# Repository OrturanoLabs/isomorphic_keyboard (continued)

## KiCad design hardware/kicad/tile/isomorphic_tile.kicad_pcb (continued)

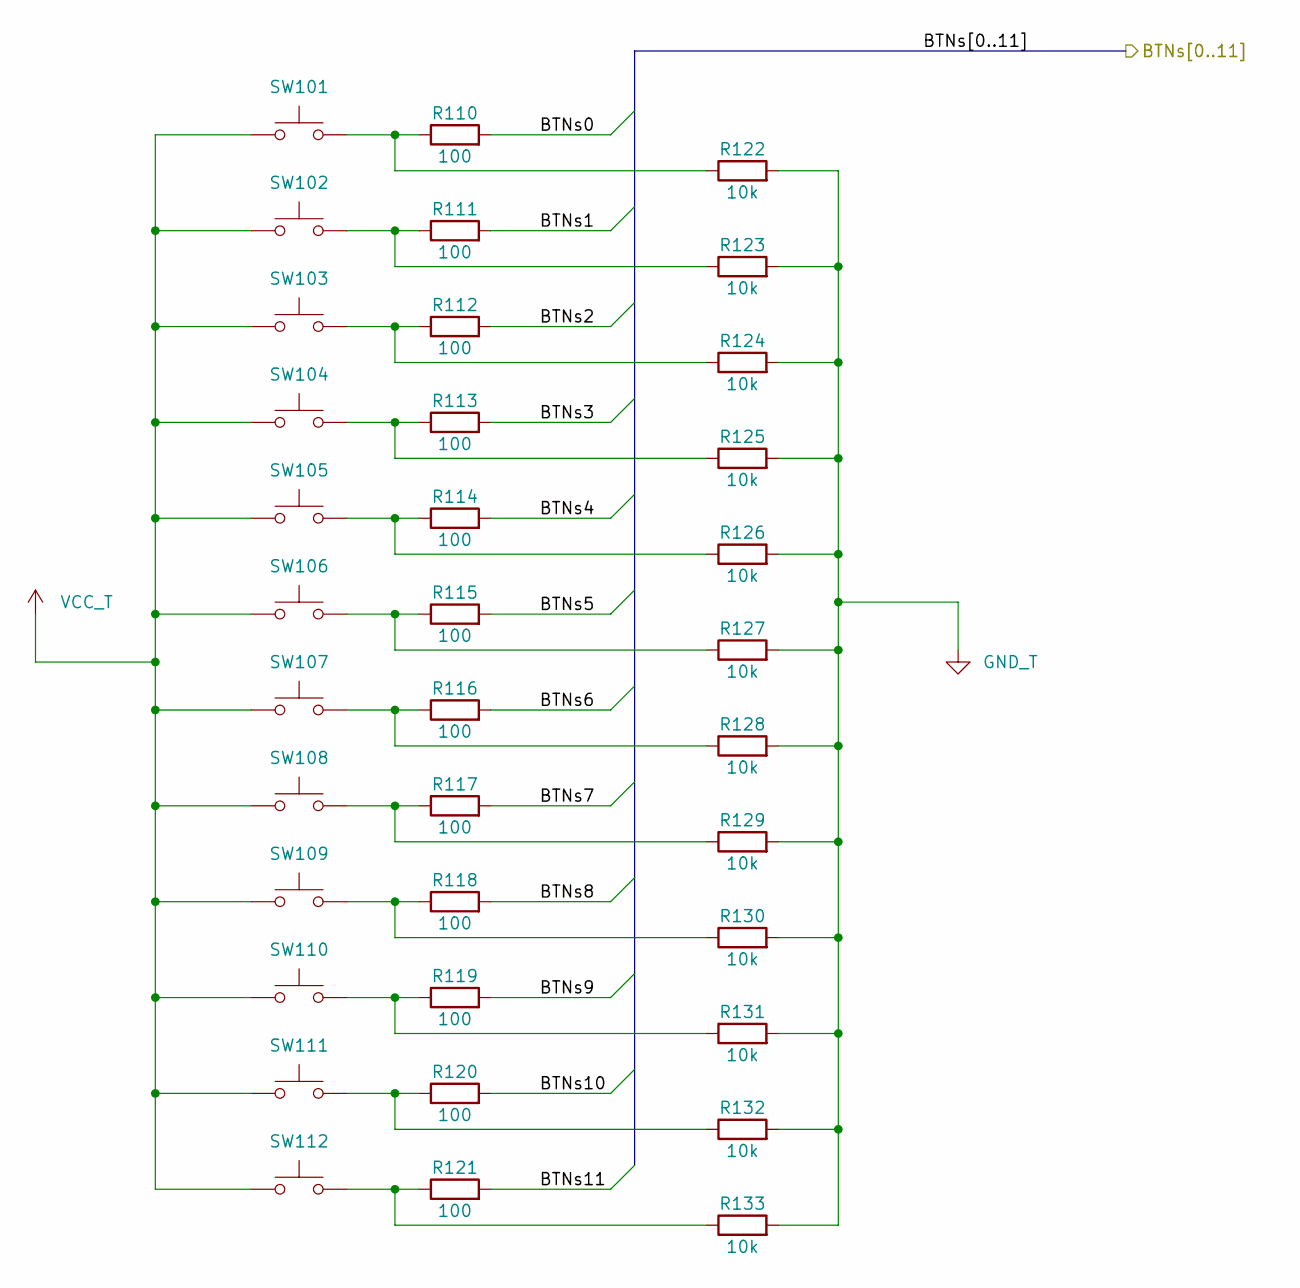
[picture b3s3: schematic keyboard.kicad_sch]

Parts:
R110, R111, R112, R113, R114, R115, R116, R117, R118, R119, R120, R121: 100; R_0603_1608Metric; MPN RC0603FR-07100RL
R122, R123, R124, R125, R126, R127, R128, R129, R130, R131, R132, R133: 10k; R_0603_1608Metric; MPN RC0603FR-0710KL
SW101, SW102, SW103, SW104, SW105, SW106, SW107, SW108, SW109, SW110, SW111, SW112: SW_Push; SW_Hotswap_Kailh_MX_1.00u_EdgeTrim; MPN CPG151101S11

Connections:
/keyboard/BTNs0: R110.2; also elsewhere on the board
/keyboard/BTNs1: R111.2; also elsewhere on the board
/keyboard/BTNs2: R112.2; also elsewhere on the board
/keyboard/BTNs3: R113.2; also elsewhere on the board
/keyboard/BTNs4: R114.2; also elsewhere on the board
/keyboard/BTNs5: R115.2; also elsewhere on the board
/keyboard/BTNs6: R116.2; also elsewhere on the board
/keyboard/BTNs7: R117.2; also elsewhere on the board
/keyboard/BTNs8: R118.2; also elsewhere on the board
/keyboard/BTNs9: R119.2; also elsewhere on the board
/keyboard/BTNs10: R120.2; also elsewhere on the board
/keyboard/BTNs11: R121.2; also elsewhere on the board
GND_T: R122.2, R123.2, R124.2, R125.2, R126.2, R127.2, R128.2, R129.2, R130.2, R131.2, R132.2, R133.2; also elsewhere on the board
unnamed: R110.1, R122.1, SW101.2
unnamed: R111.1, R123.1, SW102.2
unnamed: R112.1, R124.1, SW103.2
unnamed: R113.1, R125.1, SW104.2
unnamed: R114.1, R126.1, SW105.2
unnamed: R115.1, R127.1, SW106.2
unnamed: R116.1, R128.1, SW107.2
unnamed: R117.1, R129.1, SW108.2
unnamed: R118.1, R130.1, SW109.2
unnamed: R119.1, R131.1, SW110.2
unnamed: R120.1, R132.1, SW111.2
unnamed: R121.1, R133.1, SW112.2
VCC_T: SW101.1, SW102.1, SW103.1, SW104.1, SW105.1, SW106.1, SW107.1, SW108.1, SW109.1, SW110.1, SW111.1, SW112.1; also elsewhere on the board

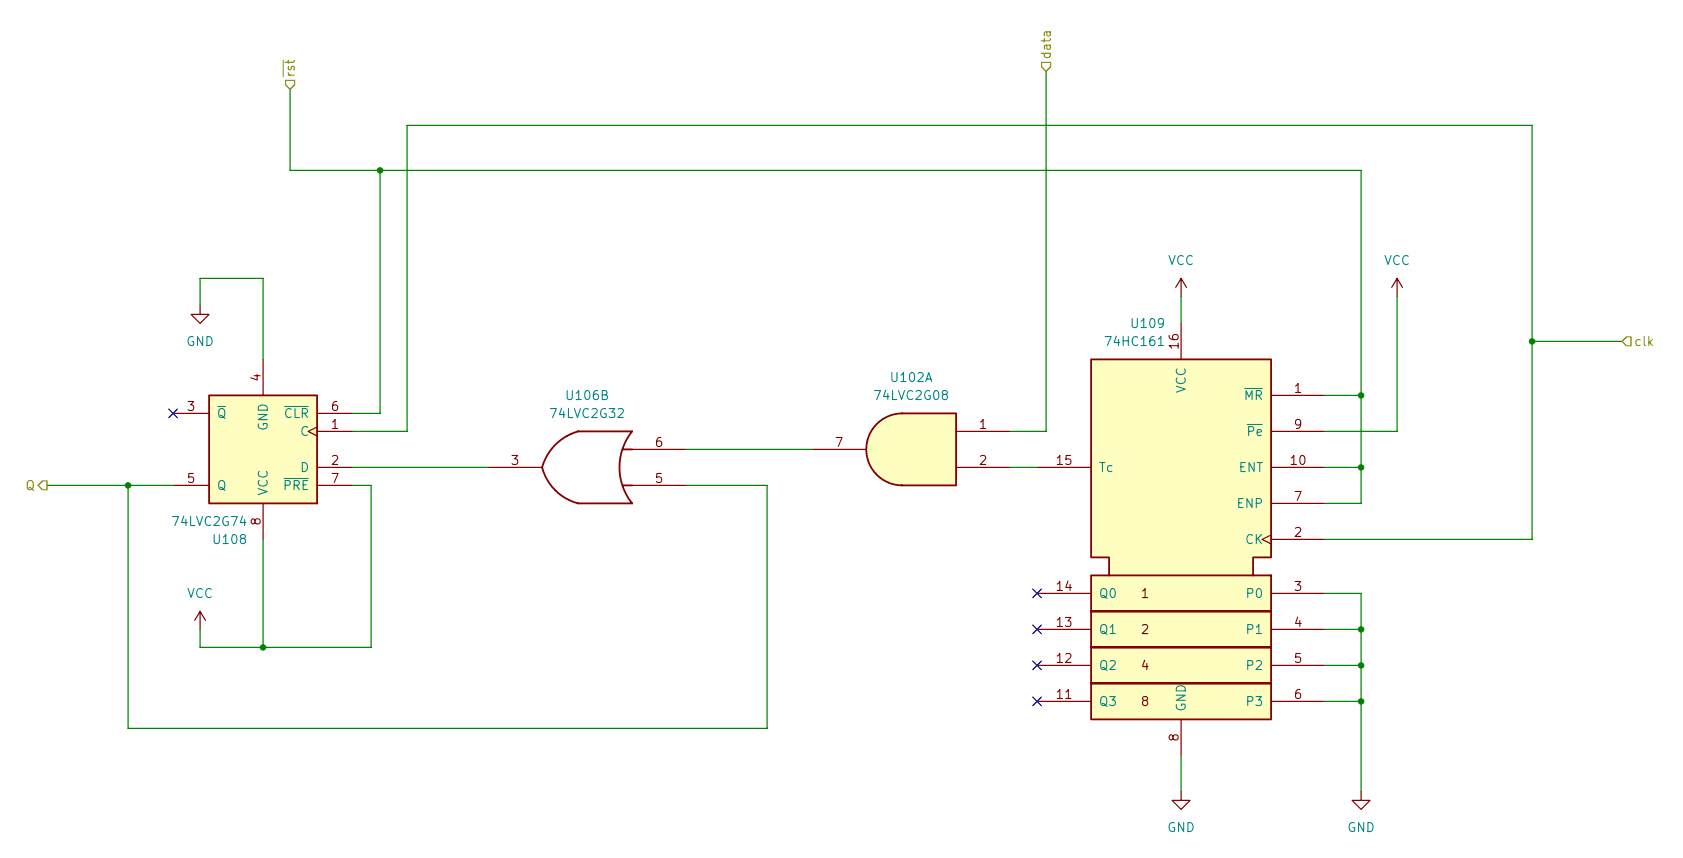
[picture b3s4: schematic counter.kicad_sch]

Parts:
U102: 74LVC2G08; SSOP-8_2.95x2.8mm_P0.65mm; MPN SN74LVC2G08DCTR
U106: 74LVC2G32; SSOP-8_2.95x2.8mm_P0.65mm; MPN SN74LVC2G32DCTR
U108: 74LVC2G74; SSOP-8_2.95x2.8mm_P0.65mm; MPN SN74LVC2G74DCTR
U109: 74HC161; SOIC-16_3.9x9.9mm_P1.27mm; MPN SN74HC161DR

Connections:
/tile/B_W_drv: U106.5, U108.5 (Q); also elsewhere on the board
/tile/B_clk: U108.1 (C), U109.2 (CK); also elsewhere on the board
/tile/counter/~rst: U108.6 (~CLR), U109.1 (~MR), U109.7 (ENP), U109.10 (ENT); also elsewhere on the board
/tile/data_drv: U102.1; also elsewhere on the board
GND: U108.4 (GND), U109.3 (P0), U109.4 (P1), U109.5 (P2), U109.6 (P3), U109.8 (GND); also elsewhere on the board
unnamed: U102.7, U106.6
unnamed: U106.3, U108.2 (D)
unnamed: U102.2, U109.15 (Tc)
VCC: U108.7 (~PRE), U108.8 (VCC), U109.9 (~Pe), U109.16 (VCC); also elsewhere on the board

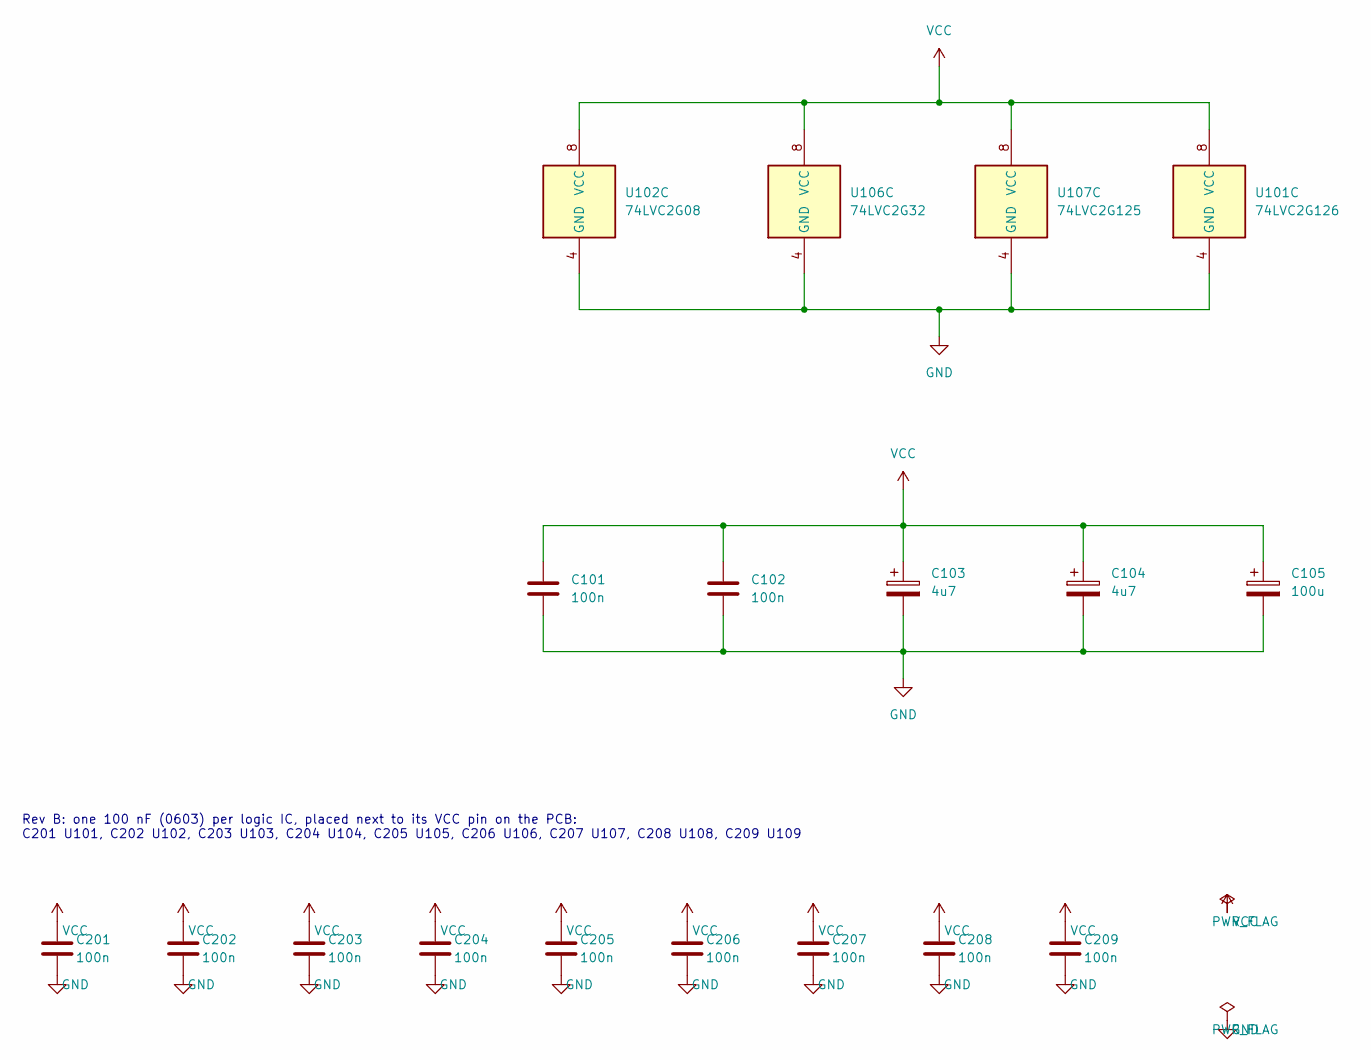
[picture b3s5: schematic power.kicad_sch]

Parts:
C101, C102, C201, C202, C203, C204, C205, C206, C207, C208, C209: 100n; C_0603_1608Metric; MPN CL10B104KB8NNNC
C103, C104: 4u7; C_1206_3216Metric; MPN CL31B475KAHNNNE
C105: 100u; CP_Elec_6.3x7.7
U101: 74LVC2G126; SSOP-8_2.95x2.8mm_P0.65mm; MPN SN74LVC2G126DCTR
U102: 74LVC2G08; SSOP-8_2.95x2.8mm_P0.65mm; MPN SN74LVC2G08DCTR
U106: 74LVC2G32; SSOP-8_2.95x2.8mm_P0.65mm; MPN SN74LVC2G32DCTR
U107: 74LVC2G125; SSOP-8_2.95x2.8mm_P0.65mm; MPN SN74LVC2G125DCTR

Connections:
GND: C101.2, C102.2, C103.2, C104.2, C105.2, C201.2, C202.2, C203.2, C204.2, C205.2, C206.2, C207.2, C208.2, C209.2, U101.4 (GND), U102.4 (GND), U106.4 (GND), U107.4 (GND); also elsewhere on the board
VCC: C101.1, C102.1, C103.1, C104.1, C105.1, C201.1, C202.1, C203.1, C204.1, C205.1, C206.1, C207.1, C208.1, C209.1, U101.8 (VCC), U102.8 (VCC), U106.8 (VCC), U107.8 (VCC); also elsewhere on the board

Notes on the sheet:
Rev B: one 100 nF (0603) per logic IC, placed next to its VCC pin on the PCB: C201 U101, C202 U102, C203 U103, C204 U104, C205 U105, C206 U106, C207 U107, C208 U108, C209 U109

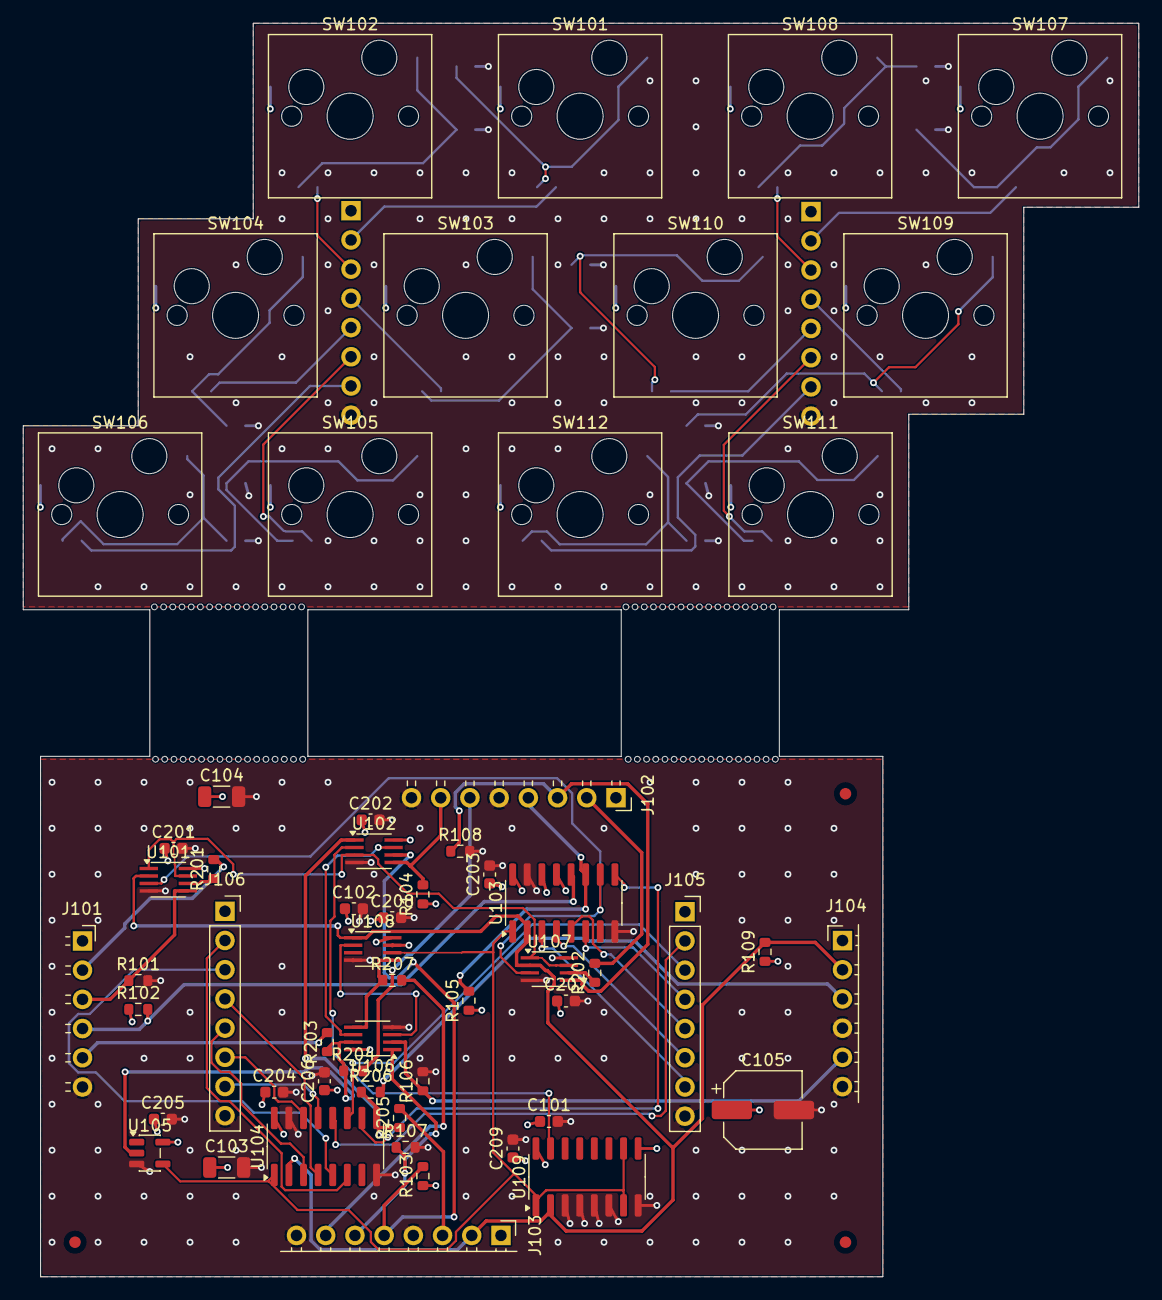
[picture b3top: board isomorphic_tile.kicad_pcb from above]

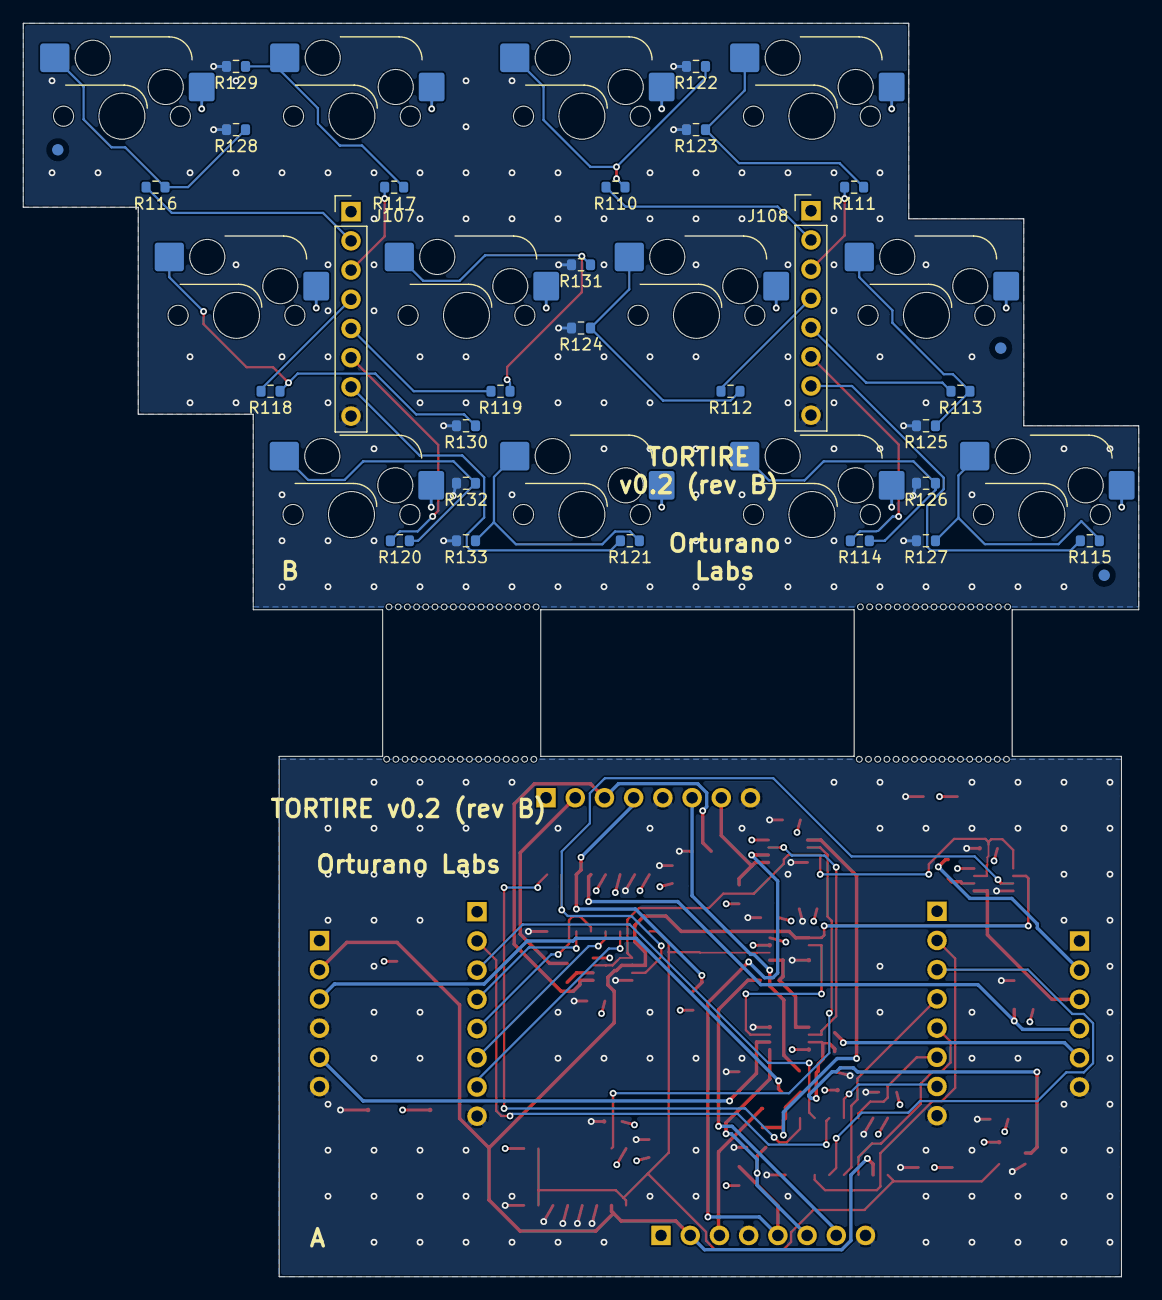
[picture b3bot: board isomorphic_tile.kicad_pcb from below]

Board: 4 copper layers, 97.0 x 109.0 mm, 157 parts (29 on the bottom side), 68 nets.

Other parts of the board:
FID1, FID2, FID3, FID4, FID5, FID6: Fiducial; Fiducial_1mm_Mask2mm
MB1, MB2, MB3, MB4, MB5, MB6, MB7, MB8, MB9, MB10, MB11, MB12, MB13, MB14, MB15, MB16, MB17, MB18, MB19, MB20, MB21, MB22, MB23, MB24, MB25, MB26, MB27, MB28, MB29, MB30, MB31, MB32, MB33, MB34, MB35, MB36, MB37, MB38, MB39, MB40, MB41, MB42, MB43, MB44, MB45, MB46, MB47, MB48, MB49, MB50, MB51, MB52, MB53, MB54, MB55, MB56, MB57, MB58, MB59, MB60, MB61, MB62, MB63, MB64, MB65, MB66, MB67, MB68: Senza-titolo; MouseBite_NPTH_0.5mm

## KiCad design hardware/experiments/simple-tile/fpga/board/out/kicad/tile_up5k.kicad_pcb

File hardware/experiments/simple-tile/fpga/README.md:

# Single-board tile: FPGA candidate experiment

One-chip-FPGA tile carrying the rev-A scan logic, replacing the 7-chip glue
+ 2x'165 + counter glue (and the 4-chip SPLD experiment) with a single FPGA.

This is an experiment, not a manufacturing-ready design. Start with
[RESULTS.md](RESULTS.md).

## Layout

- `rtl/tile_fpga.vhdl` — device-independent tile core (DUT). Selectable
  `SNAP_MODE`: "fall" (default; negedge-latch snapshot = rev-A capture
  instant, no oscillator needed) or "track" (sysclk sampling while the latch
  is high; documented approximation with a characterised dead zone).
  First-bit-before-first-clock preserved combinationally; true tri-state
  clock outputs; see docs/clock_domains.md.
- `rtl/top_{gw1nz,ice40up,ice40lp}.vhdl` + `top_*_track.vhdl` — board-level
  tops per device per mode (oscillator instantiated only for "track";
  ghdl-plugin takes no `-g`, hence the mode variants).
- `sim/` — self-checking benches + runner (`run_sims.sh`): unit scenarios
  (incl. S8 phase-sweep CHARACTERISATION), paired REF-vs-DUT grids in both
  modes, mutations.
- `rtl/top_{gw1nz,ice40up,ice40lp}.vhdl` — board-level tops: on-chip osc
  (OSCZ / SB_HFOSC) or module osc, merged connector nets, pruned straps.
- `sim/` — self-checking benches + runner (`run_sims.sh`): unit scenarios
  and paired REF(rev-A model)-vs-DUT grids with mutations.
- `synth/` — pin maps + `run_synth.sh` full flows to bitstreams.
- `docs/` — [pin budget](docs/pin_budget.md),
  [alternatives incl. TinyFPGA](docs/alternatives.md),
  [power/BOM](docs/power_bom.md), [clock domains](docs/clock_domains.md).
- `results/logs/` — pinned environment + real run logs; `results/build/`
  holds netlists/.fs/.bin (git-ignored).

## Reproduce (from the repository root)

```sh
bash hardware/experiments/simple-tile/fpga/sim/run_sims.sh
bash hardware/experiments/simple-tile/fpga/synth/run_synth.sh
```

Both use `tools/oss.sh` (container `localhost/oss-cad-suite:2026-09-26`),
falling back to host ghdl/yosys/nextpnr/apycula if installed.

References stay where they were: `hardware/simulation/` (rev-A models),
`docs/architecture/protocol.md`, `../regression/` (frames + topologies),
`../logic/` (discrete/SPLD/CPLD experiments + timing census).

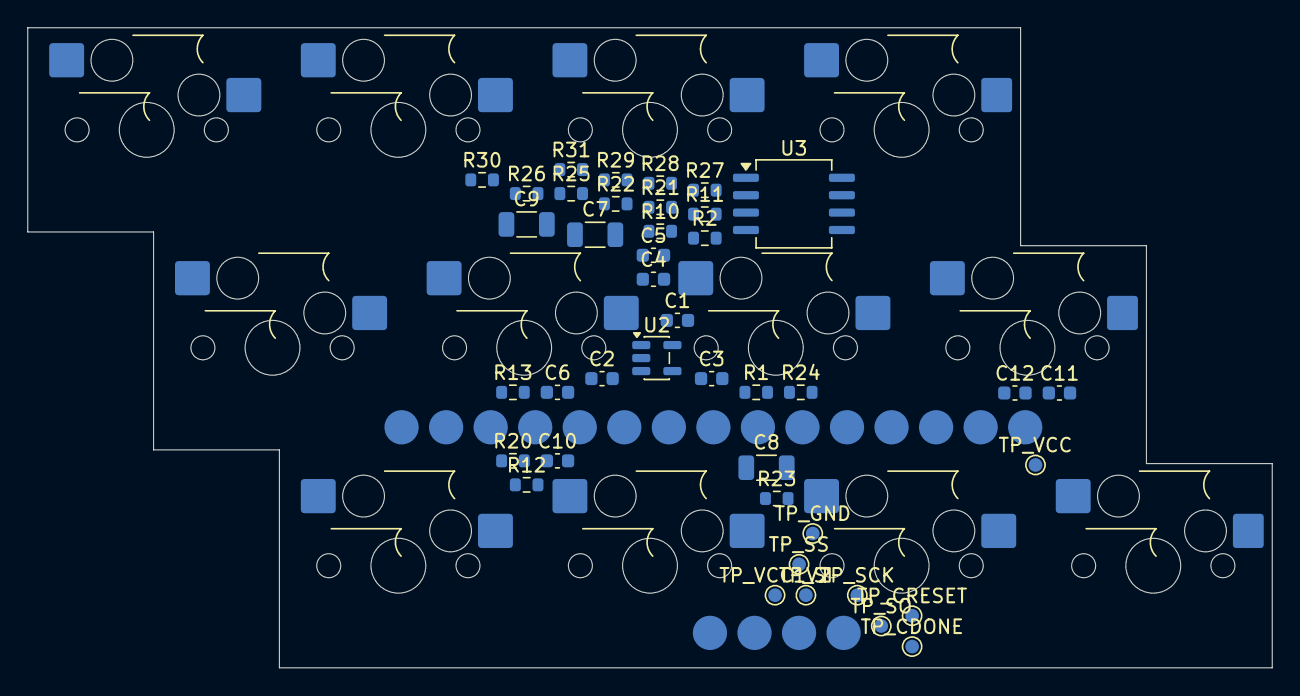
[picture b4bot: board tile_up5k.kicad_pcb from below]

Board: 2 copper layers, 90.8 x 46.7 mm, 72 parts (60 on the bottom side), 25 nets, no tracks yet.

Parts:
C1: 100n; C1
C2: 100n; C2
C3: 100n; C3
C4: 100n; C4
C5: 100n; C5
C6: 100n; C6
C7: 4u7; C7
C8: 4u7; C8
C9: 4u7; C9
C10: 100n; C10
C11: 1u; C11
C12: 1u; C12
JP_B_W: PAD2.5; JP_B_W
JP_B_clk: PAD2.5; JP_B_clk
JP_B_data: PAD2.5; JP_B_data
JP_B_first: PAD2.5; JP_B_first
JP_B_latch: PAD2.5; JP_B_latch
JP_GND: PAD2.5; JP_GND
JP_GND_DET_B: PAD2.5; JP_GND_DET_B
JP_GND_DET_R: PAD2.5; JP_GND_DET_R
JP_GND_DET_T: PAD2.5; JP_GND_DET_T
JP_L_clk: PAD2.5; JP_L_clk
JP_L_data: PAD2.5; JP_L_data
JP_L_endrow: PAD2.5; JP_L_endrow
JP_L_latch: PAD2.5; JP_L_latch
JP_R_latch: PAD2.5; JP_R_latch
JP_T_W: PAD2.5; JP_T_W
JP_T_clk: PAD2.5; JP_T_clk
JP_T_data: PAD2.5; JP_T_data
JP_T_endcol: PAD2.5; JP_T_endcol
JP_VCC: PAD2.5; JP_VCC
R1: 10k; R1
R2: 100; R2
R10: 10k; R10
R11: 10k; R11
R12: 10k; R12
R13: 10k; R13
R20: 10k; R20
R21: 10k; R21
R22: 10k; R22
R23: 10k; R23
R24: 10k; R24
R25: 10k; R25
R26: 10k; R26
R27: 10k; R27
R28: 10k; R28
R29: 10k; R29
R30: 10k; R30
R31: 10k; R31
SW1: Kailh MX hotswap; SW1
SW2: Kailh MX hotswap; SW2
SW3: Kailh MX hotswap; SW3
SW4: Kailh MX hotswap; SW4
SW5: Kailh MX hotswap; SW5
SW6: Kailh MX hotswap; SW6
SW7: Kailh MX hotswap; SW7
SW8: Kailh MX hotswap; SW8
SW9: Kailh MX hotswap; SW9
SW10: Kailh MX hotswap; SW10
SW11: Kailh MX hotswap; SW11
SW12: Kailh MX hotswap; SW12
TP_CDONE: CFG_DONE; TP_CDONE
TP_CRESET: CFG_CRESET; TP_CRESET
TP_GND: GND; TP_GND
TP_SCK: SPI_SCK; TP_SCK
TP_SI: SPI_SI; TP_SI
TP_SO: SPI_SO; TP_SO
TP_SS: SPI_SS; TP_SS
TP_VCC: VCC; TP_VCC
TP_VCC1V2: VCC1V2; TP_VCC1V2
U2: TLV75512PDBVR; U2
U3: SPI-FLASH; U3

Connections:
B_latch: JP_B_latch.1, R12.1
CFG_CRESET: R1.1, TP_CRESET.1
GND: C1.2, C2.2, C3.2, C4.2, C5.2, C6.2, C7.2, C8.2, C9.2, C10.2, C11.2, C12.2, JP_GND.1, JP_GND_DET_B.1, JP_GND_DET_R.1, JP_GND_DET_T.1, R10.2, R11.2, R12.2, R13.2, R20.2, R21.2, R22.2, R23.2, R24.2, R25.2, R26.2, R27.2, R28.2, R29.2, R30.2, R31.2, TP_GND.1, U2.2, U3.4
K1: R20.1, SW1.2
K2: R21.1, SW2.2
K3: R22.1, SW3.2
K4: R23.1, SW4.2
K5: R24.1, SW5.2
K6: R25.1, SW6.2
K7: R26.1, SW7.2
K8: R27.1, SW8.2
K9: R28.1, SW9.2
K10: R29.1, SW10.2
K11: R30.1, SW11.2
K12: R31.1, SW12.2
L_data: JP_L_data.1, R11.1
R_latch: JP_R_latch.1, R13.1
SPI_SCK: TP_SCK.1, U3.6
SPI_SI: TP_SI.1, U3.5
SPI_SO: TP_SO.1, U3.2
SPI_SS: TP_SS.1, U3.1
T_data: JP_T_data.1, R10.1
VCC: C3.1, C4.1, C5.1, C6.1, C8.1, C11.1, JP_VCC.1, R1.2, SW1.1, SW2.1, SW3.1, SW4.1, SW5.1, SW6.1, SW7.1, SW8.1, SW9.1, SW10.1, SW11.1, SW12.1, TP_VCC.1, U2.1, U2.3, U3.3, U3.7, U3.8
VCC1V2: C1.1, C2.1, C7.1, C12.1, R2.1, TP_VCC1V2.1, U2.5
VCCPLL_1V2: C9.1, C10.1, R2.2

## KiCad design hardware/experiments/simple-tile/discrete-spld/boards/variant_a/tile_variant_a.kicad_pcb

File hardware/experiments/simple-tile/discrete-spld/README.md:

# discrete-spld — pin-level discrete-glue tile candidates

Two tile-logic candidates on the simple-tile frame (18.36 mm equilateral MX
lattice, drop-in chassis, no tile-side MCU/LED/Hall, 20 MHz shift clock,
16 tiles max), carried from machine-readable pin-level circuits to
protocol-level proofs to KiCad placement boards:

| variant | glue ICs | total ICs | functional proof | placement on the dense tile |
|---|---|---|---|---|
| A — all-LVC + SN74LV161A + 2x LVC165A | 7 | 9 | PASS (33-config suite) | full placement, 0 DRC errors |
| A2 — A with 2x LVC2G241 for the buffer pair | 7 | 9 | PASS (same suite) | (netlist-equivalent to A) |
| B2 — ATF22LV10C-10 (truez) + 2x LVC165A + 1G04 | 2 | 4 | PASS (suite on the DECODED fuse map) | all placed EXCEPT the GAL: TSSOP-24 fits no lane-clear free rect (see rotation study) |

Interface: the **connector-next aggregate 19-contact** plan (14 signals +
VCC + GND + 3 detect-GND pads, straps removed), used at its published
coordinates; `T_latch`/`R_data` legs of the old 28-pad plan are folded into
`L_latch`/`B_data` as the budget worker specifies (5 x 33R series now, not
7).

## Layout

* `circuits/` — the pin-level circuit JSONs (`schema.md` documents the
  format).  `reva_reference.json` is the rev-A export with the interface
  block completed + verified by `tools/keymap_check.py`.  `variant_a.json`,
  `variant_a2.json`, `variant_b2.json` are authored in
  `tools/gen_circuits.py` on rev-A's passive plan.
* `results/` — every check output (see below).
* `boards/` — generated KiCad boards (placement prototypes, unrouted by
  design) + placement/DRC reports.
* `tools/` — the toolchain (python stdlib only).

## Verification pipeline (all re-runnable)

```
python3 tools/keymap_check.py        # rev-A keymap+interface assertions
python3 tools/gen_circuits.py        # variant circuits
python3 tools/jeddec.py ...          # GAL22V10 fuse-map decoder (galette+jedutil cross-validated)
python3 tools/galcheck.py ...        # fuses vs source equations, exhaustive
python3 tools/sim_tile.py [--quick|--shapes ...|--circuits ...|--modes ...]
python3 tools/bom_check.py           # BOM census vs rev-A
python3 tools/rotation_study.py      # socket rotation / GAL-fit study
python3 tools/board_gen.py           # KiCad boards + placement + coll. checks
tools/kicad-cli.sh pcb drc boards/<v>/tile_<v>.kicad_pcb --format json --output boards/<v>/drc_raw.json
python3 tools/build_costs.py         # costs table (sourced-or-unknown)
```

Note: the full sim suite takes ~3.5 min; the earlier 120 s timeout was a
shell limit, not a failure — the complete run is recorded in
results/sim_suite.txt (33/33 PASS).  `--quick` finishes in seconds.

## Result index

| file | content |
|---|---|
| `results/keymap_check.txt` | rev-A keymap/pin map verification (all PASS) |
| `results/jeddec_{truez,golden}.txt` | fuse-map decode + checksums OK |
| `results/galcheck_{truez,golden}.txt` | 20/20 equation MATCH each |
| `results/sim_suite.txt` | 33/33 protocol configs PASS (3 variants) |
| `results/fewer_ics.md` | IC-count survey, corrected (no minimum claimed) |
| `results/bom_check.txt` | BOM census |
| `results/costs.{json,md}` | costs per tile (prices unknown — blocked fetches; MPNs datasheet-confirmed) |
| `results/programmer_gap.md` | ATF22LV10C programming gap report + bench plan |
| `results/rotation_study.{txt,md}` | socket-rotation feasibility + relaxed-pitch quantification |
| `results/boards_drc.md` | DRC digests (0 errors both boards) |
| `results/battery.log` | last full end-to-end battery output |

## Answers (current state)

1. **Faithful pin-level A and B2 circuits: done and simulation-proven**;
   B2's GAL behaviour comes from the decoded fuse map, not the source
   assumption.
2. **Fewer discrete parts:** 9-IC baseline (7 glue + 2 SR) is a working
   *partition*, not a proven minimum; surveyed swaps are count-neutral
   (`results/fewer_ics.md`).  The real consolidation is B2's SPLD route
   (4 ICs), blocked on geometry as quantified below.
3. **Boards:** both are placement prototypes with **0 DRC errors** under
   kicad-cli 10.0.6 (only cosmetic silk warnings; unconnected counts are
   the honest unrouted totals: vA 175 items / ~52+empty nets, vB2 129/48).
   Board copies normalize the vendored Kailh socket's courtyard to a closed
   B-side polygon (documented in board_gen.py) — the vendored lib is not
   touched.
4. **Socket rotation for the GAL** (tasked exploration): 180 deg rotation
   is mechanically legal here (documented), opens 63.25x11 mm undersides in
   some patterns, but every lane-clean pattern still misses the 7.7x8.3 mm
   GAL courtyard (0/64 structured candidates; the connector-next lanes are
   fixed).  Relaxed-pitch requirement quantified: P' >= 18.91 mm (+0.55,
   +3.0%) opens an 8.3 mm island, collision-free with all six neighbours at
   that pitch — chassis rebudget required; classified as the relaxed-pitch
   path, not pursued further here.
5. **Programmer gap** for ATF22LV10C: documented with upstream evidence
   (`results/programmer_gap.md`); no hardware touched.
6. **Layer count note:** 2-layer placement prototypes; no 6-layer option
   proposed anywhere (if routing ever happens, 4 layers is the family
   target — recorded as a note only).

## Integrity notes

* No fabrication or timing sign-off is claimed anywhere; these are
  placement prototypes + logic proofs.
* The boards are 2-layer, 1.6 mm, per the frame; all DRC classes are
  itemised in results/boards_drc.md with classifications.
* Prices are 'unknown' with recorded fetch evidence - no invented numbers.
* The rev-A BOM check found no symbol/silicon pinout errors (incl. the
  2G74 SM8 single-FF question, resolved per TI SCES203Q).

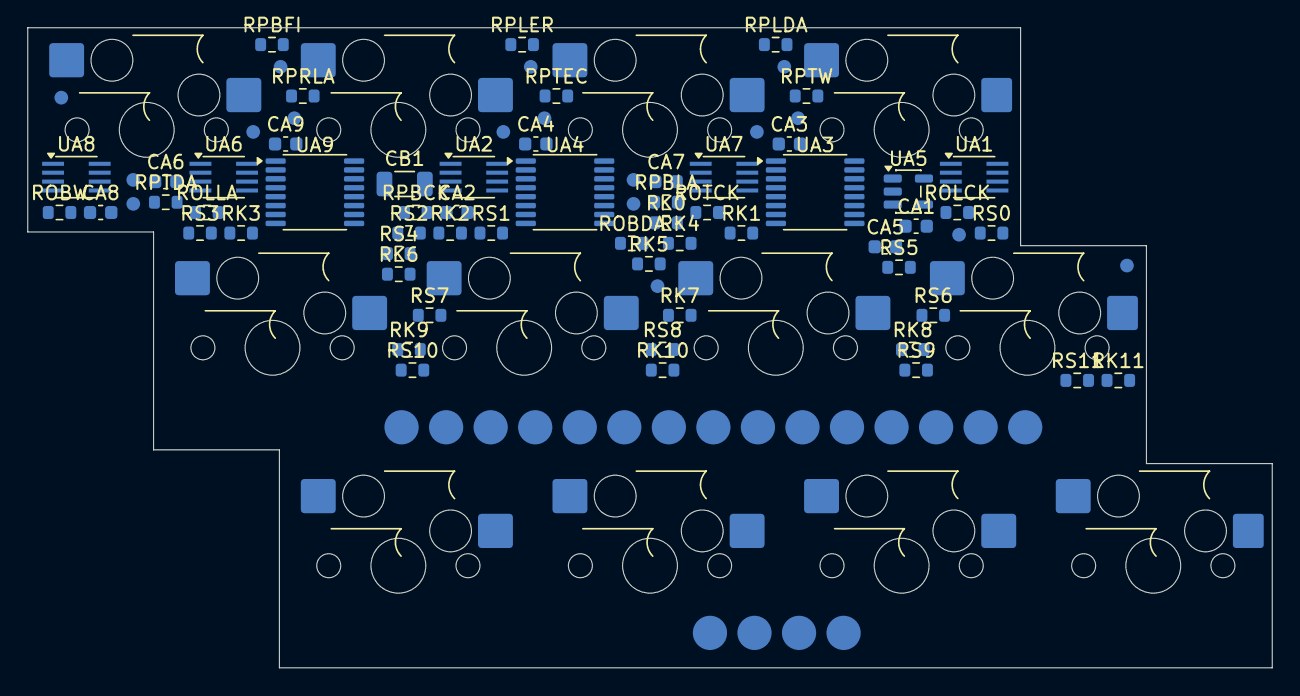
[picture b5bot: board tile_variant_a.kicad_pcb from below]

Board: 2 copper layers, 90.8 x 46.7 mm, 105 parts (93 on the bottom side), 52 nets, no tracks yet.

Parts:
CA1: 100n; CA1
CA2: 100n; CA2
CA3: 100n; CA3
CA4: 100n; CA4
CA5: 100n; CA5
CA6: 100n; CA6
CA7: 100n; CA7
CA8: 100n; CA8
CA9: 100n; CA9
CB1: 4u7; CB1
JP_B_W: PAD2.5; JP_B_W
JP_B_clk: PAD2.5; JP_B_clk
JP_B_data: PAD2.5; JP_B_data
JP_B_first: PAD2.5; JP_B_first
JP_B_latch: PAD2.5; JP_B_latch
JP_GND: PAD2.5; JP_GND
JP_GND_DET_B: PAD2.5; JP_GND_DET_B
JP_GND_DET_R: PAD2.5; JP_GND_DET_R
JP_GND_DET_T: PAD2.5; JP_GND_DET_T
JP_L_clk: PAD2.5; JP_L_clk
JP_L_data: PAD2.5; JP_L_data
JP_L_endrow: PAD2.5; JP_L_endrow
JP_L_latch: PAD2.5; JP_L_latch
JP_R_latch: PAD2.5; JP_R_latch
JP_T_W: PAD2.5; JP_T_W
JP_T_clk: PAD2.5; JP_T_clk
JP_T_data: PAD2.5; JP_T_data
JP_T_endcol: PAD2.5; JP_T_endcol
JP_VCC: PAD2.5; JP_VCC
RK0: 10k; RK0
RK1: 10k; RK1
RK2: 10k; RK2
RK3: 10k; RK3
RK4: 10k; RK4
RK5: 10k; RK5
RK6: 10k; RK6
RK7: 10k; RK7
RK8: 10k; RK8
RK9: 10k; RK9
RK10: 10k; RK10
RK11: 10k; RK11
ROBDA: 33; ROBDA
ROBW: 33; ROBW
ROLCK: 33; ROLCK
ROLLA: 33; ROLLA
ROTCK: 33; ROTCK
RPBCK: 10k; RPBCK
RPBFI: 10k; RPBFI
RPBLA: 10k; RPBLA
RPLDA: 10k; RPLDA
RPLER: 10k; RPLER
RPRLA: 10k; RPRLA
RPTDA: 10k; RPTDA
RPTEC: 10k; RPTEC
RPTW: 10k; RPTW
RS0: 100; RS0
RS1: 100; RS1
RS2: 100; RS2
RS3: 100; RS3
RS4: 100; RS4
RS5: 100; RS5
RS6: 100; RS6
RS7: 100; RS7
RS8: 100; RS8
RS9: 100; RS9
RS10: 100; RS10
RS11: 100; RS11
SW1: SW; SW1
SW2: SW; SW2
SW3: SW; SW3
SW4: SW; SW4
SW5: SW; SW5
SW6: SW; SW6
SW7: SW; SW7
SW8: SW; SW8
SW9: SW; SW9
SW10: SW; SW10
SW11: SW; SW11
SW12: SW; SW12
TP_B_W: B_W; TP_B_W
TP_B_clk: B_clk; TP_B_clk
TP_B_data: B_data; TP_B_data
TP_B_first: B_first; TP_B_first
TP_B_latch: B_latch; TP_B_latch
TP_GND: GND; TP_GND
TP_L_clk: L_clk; TP_L_clk
TP_L_data: L_data; TP_L_data
TP_L_latch: L_latch; TP_L_latch
TP_R_latch: R_latch; TP_R_latch
TP_T_clk: T_clk; TP_T_clk
TP_T_data: T_data; TP_T_data
TP_VCC: VCC; TP_VCC
TP_W: W; TP_W
TP_data_drv: data_drv; TP_data_drv
TP_latch_drv: latch_drv; TP_latch_drv
TP_nRST: nRST; TP_nRST
UA1: SN74LVC2G126; UA1
UA2: SN74LVC2G08; UA2
UA3: SN74LVC165A; UA3
UA4: SN74LVC165A; UA4
UA5: SN74LVC1G04; UA5
UA6: SN74LVC2G32; UA6
UA7: SN74LVC2G125; UA7
UA8: SN74LVC2G74; UA8
UA9: SN74LV161A; UA9

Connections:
B_W: JP_B_W.1, ROBW.2, TP_B_W.1
B_W_drv: ROBW.1, UA6.5, UA8.5
B_clk: JP_B_clk.1, RPBCK.1, TP_B_clk.1, UA1.2, UA3.2, UA4.2, UA7.2, UA8.1, UA9.2
B_data: JP_B_data.1, ROBDA.2, TP_B_data.1
B_first: JP_B_first.1, RPBFI.1, TP_B_first.1, UA2.6
B_latch: JP_B_latch.1, RPBLA.1, TP_B_latch.1, UA6.1
CHAIN: UA3.9, UA4.10
DS_net: UA1.3, UA3.10, UA7.3
GND: CA1.2, CA2.2, CA3.2, CA4.2, CA5.2, CA6.2, CA7.2, CA8.2, CA9.2, CB1.2, JP_GND.1, JP_GND_DET_B.1, JP_GND_DET_R.1, JP_GND_DET_T.1, RK0.2, RK1.2, RK2.2, RK3.2, RK4.2, RK5.2, RK6.2, RK7.2, RK8.2, RK9.2, RK10.2, RK11.2, RPBLA.2, RPLDA.2, RPRLA.2, RPTDA.2, TP_GND.1, UA1.4, UA2.4, UA3.8, UA3.15, UA4.8, UA4.15, UA5.3, UA6.4, UA7.4, UA8.4, UA9.3, UA9.4, UA9.5, UA9.6, UA9.8
KEY0: RS0.2, UA4.6
KEY1: RS1.2, UA4.5
KEY2: RS2.2, UA4.4
KEY3: RS3.2, UA4.3
KEY4: RS4.2, UA4.14
KEY5: RS5.2, UA4.13
KEY6: RS6.2, UA4.12
KEY7: RS7.2, UA4.11
KEY8: RS8.2, UA3.6
KEY9: RS9.2, UA3.5
KEY10: RS10.2, UA3.4
KEY11: RS11.2, UA3.3
L_clk: JP_L_clk.1, ROLCK.2, TP_L_clk.1
L_clk_drv: ROLCK.1, UA1.6
L_data: JP_L_data.1, RPLDA.1, TP_L_data.1, UA1.5
L_endrow: JP_L_endrow.1, RPLER.1, UA3.12
L_latch: JP_L_latch.1, ROLLA.2, TP_L_latch.1
R_latch: JP_R_latch.1, RPRLA.1, TP_R_latch.1, UA6.2
SWN0: RK0.1, RS0.1, SW1.2
SWN1: RK1.1, RS1.1, SW2.2
SWN2: RK2.1, RS2.1, SW3.2
SWN3: RK3.1, RS3.1, SW4.2
SWN4: RK4.1, RS4.1, SW5.2
SWN5: RK5.1, RS5.1, SW6.2
SWN6: RK6.1, RS6.1, SW7.2
SWN7: RK7.1, RS7.1, SW8.2
SWN8: RK8.1, RS8.1, SW9.2
SWN9: RK9.1, RS9.1, SW10.2
SWN10: RK10.1, RS10.1, SW11.2
SWN11: RK11.1, RS11.1, SW12.2
T_W: JP_T_W.1, RPTW.1, UA2.5
T_clk: JP_T_clk.1, ROTCK.2, TP_T_clk.1
T_clk_drv: ROTCK.1, UA7.6
T_data: JP_T_data.1, RPTDA.1, TP_T_data.1, UA7.5
T_endcol: JP_T_endcol.1, RPTEC.1, UA3.11
Tc: UA2.2, UA9.15
VCC: CA1.1, CA2.1, CA3.1, CA4.1, CA5.1, CA6.1, CA7.1, CA8.1, CA9.1, CB1.1, JP_VCC.1, RPBCK.2, RPBFI.2, RPLER.2, RPTEC.2, RPTW.2, SW1.1, SW2.1, SW3.1, SW4.1, SW5.1, SW6.1, SW7.1, SW8.1, SW9.1, SW10.1, SW11.1, SW12.1, TP_VCC.1, UA1.8, UA2.8, UA3.13, UA3.14, UA3.16, UA4.16, UA5.5, UA6.8, UA7.8, UA8.7, UA8.8, UA9.9, UA9.16
W: TP_W.1, UA1.1, UA1.7, UA2.3, UA7.1, UA7.7
data_drv: ROBDA.1, TP_data_drv.1, UA2.1, UA4.9
flag_and: UA2.7, UA6.6
flag_d: UA6.3, UA8.2
latch_drv: ROLLA.1, TP_latch_drv.1, UA5.2, UA6.7
nRST: TP_nRST.1, UA3.1, UA4.1, UA5.4, UA8.6, UA9.1, UA9.7, UA9.10

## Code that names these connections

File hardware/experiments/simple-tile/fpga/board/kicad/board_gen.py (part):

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

def tile_net_of_gw1nz(net):
    m = {"clk_pin": "B_clk", "t_w_pin": "T_W", "t_endcol_pin": "T_endcol",
         "b_first_pin": "B_first", "l_endrow_pin": "L_endrow",
         "t_data_pin": "T_data", "l_data_pin": "L_data",
         "b_latch_pin": "B_latch", "r_latch_pin": "R_latch",
         "t_clk_pin": "T_clk", "l_clk_pin": "L_clk", "latcho_pin": "L_latch",
         "dout_pin": "B_data", "b_w_pin": "B_W"}
    if net.startswith("keys["):
        return key_net(int(net[5:-1]))
    return m[net]
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        {"ref": "C8", "fp": "C0603", "value": "1u", "pins": {"1": "VCC1V2_RAW", "2": "GND"}, "note": "TLV755P COUT >= 1uF at the OUT pin BEFORE the bead (SBVS320D 5.3/Table 4-1); without it the bead isolates all bypass from the LDO (found 2026-10-14)", "anchor_net": "VCC"},
        {"ref": "C9", "fp": "C0603", "value": "1u", "pins": {"1": "VCC", "2": "GND"}, "note": "TLV755P CIN >= 1uF at the IN pin (SBVS320D Table 4-1 'required')", "anchor_net": "VCC"},
        {"ref": "FB1", "fp": "R0603", "value": "FB 120R@100M", "pins": {"1": "VCC1V2_RAW", "2": "VCC1V2"}, "note": "core-rail noise filter (UG293: FB class MH2029-221Y) between LDO OUT (VCC1V2_RAW) and the FPGA core pins (VCC1V2) + C6", "anchor_fpga_pin": "12"},
        {"ref": "R1", "fp": "R0603", "value": "1k", "pins": {"1": "MODE0", "2": "GND"}, "note": "MODE0=0 auto-boot strap (UG293)", "anchor_fpga_pin": "43"},
        {"ref": "R2", "fp": "R0603", "value": "1k", "pins": {"1": "MODE1", "2": "GND"}, "note": "MODE1=0 auto-boot strap (UG293)", "anchor_fpga_pin": "42"},
        {"ref": "R3", "fp": "R0603", "value": "4k7", "pins": {"1": "JTAG_TCK", "2": "GND"}, "note": "TCK pull-down (UG293)", "anchor_fpga_pin": "3"},
        {"ref": "R4", "fp": "R0603", "value": "4k7", "pins": {"1": "CFG_READY", "2": "VCC"}, "anchor_fpga_pin": "45"},
        {"ref": "R5", "fp": "R0603", "value": "4k7", "pins": {"1": "CFG_DONE", "2": "VCC"}, "anchor_fpga_pin": "46"},
        {"ref": "R6", "fp": "R0603", "value": "4k7", "pins": {"1": "CFG_RECONFIG", "2": "VCC"}, "anchor_fpga_pin": "48"},
        *SERIES_PARTS_GW1NZ,
    ]
    return parts
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def fpga_nets_up5k(pins):
    db = json.load(open(os.path.join(BOARD, "data", "pins_ice40up_sg48.json")))
    nets = {}
    tile_up = {"clk_pin": "B_clk", "t_w_pin": "T_W", "t_endcol_pin": "T_endcol",
               "b_first_pin": "B_first", "l_endrow_pin": "L_endrow",
               "t_data_pin": "T_data", "l_data_pin": "L_data",
               "b_latch_pin": "B_latch", "r_latch_pin": "R_latch",
               "t_clk_pin": "T_clk", "l_clk_pin": "L_clk",
               "latcho_pin": "L_latch", "dout_pin": "B_data", "b_w_pin": "B_W"}
    for n, pads in pins.items():
        nets[str(pads[0])] = (key_net(int(n[5:-1])) if n.startswith("keys[")
                              else tile_up[n])
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         "pins": {"1": "VCC", "2": "GND", "3": "VCC", "5": "VCC1V2"},
         "note": "TI TLV755P 500mA LDO, fixed 1.2V, SOT-23-5(DBV); pinout VERIFIED vs TI SBVS320D Table 4-1: 1=IN 2=GND 3=EN 4=NC 5=OUT; CIN/COUT >= 1uF required -> C11 at IN, existing C1/C2/C7+C12 at OUT"},
        {"ref": "U3", "fp": "SOIC8", "value": "SPI-FLASH",
         "pins": {"1": "SPI_SS", "2": "SPI_SO", "3": "VCC", "4": "GND",
                  "5": "SPI_SI", "6": "SPI_SCK", "7": "VCC", "8": "VCC"},
         "note": "SOIC-8 config flash 3.3V, >=1 Mbit reprogrammable (W25Q80 class; part TBD); in-circuit: hold CRESET_B low -> FPGA SPI IOs tri-stated (DS 4.6)", "anchor_fpga_pin": "15"},
        {"ref": "C1", "fp": "C0603", "value": "100n", "pins": {"1": "VCC1V2", "2": "GND"}, "anchor_fpga_pin": "5"},
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        {"ref": "C6", "fp": "C0603", "value": "100n", "pins": {"1": "VCC", "2": "GND"}, "anchor_fpga_pin": "24"},
        {"ref": "C7", "fp": "C1206", "value": "4u7", "pins": {"1": "VCC1V2", "2": "GND"}, "anchor_fpga_pin": "5"},
        {"ref": "C8", "fp": "C1206", "value": "4u7", "pins": {"1": "VCC", "2": "GND"}, "anchor_fpga_pin": "22"},
        {"ref": "R1", "fp": "R0603", "value": "10k", "pins": {"1": "CFG_CRESET", "2": "VCC"}, "note": "CRESET_B pure input, no internal pull (TN02001)", "anchor_fpga_pin": "8"},
        {"ref": "R2", "fp": "R0603", "value": "100", "pins": {"1": "VCC1V2", "2": "VCCPLL_1V2"}, "note": "VCCPLL RC filter (TN02006): 100ohm + C3(4u7)+C9(100n)", "anchor_fpga_pin": "29"},
        {"ref": "C9", "fp": "C1206", "value": "4u7", "pins": {"1": "VCCPLL_1V2", "2": "GND"}, "anchor_fpga_pin": "29"},
        {"ref": "C10", "fp": "C0603", "value": "100n", "pins": {"1": "VCCPLL_1V2", "2": "GND"}, "anchor_fpga_pin": "29"},
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
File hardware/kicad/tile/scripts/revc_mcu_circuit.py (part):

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
# ATtiny1616-MNR VQFN-20 3x3 mm, 0.40 mm pitch, 1.7 mm exposed pad (DS40002204A 4.3, 39.4);
# the SOIC-20 wide version (about 13 x 10 mm) does not fit between the sockets and LEDs
PIN = {"PA2": 1, "PA3": 2, "GND": 3, "VDD": 4, "PA4": 5, "PA5": 6, "PA6": 7, "PA7": 8,
       "PB5": 9, "PB4": 10, "PB3": 11, "PB2": 12, "PB1": 13, "PB0": 14, "PC0": 15, "PC1": 16,
       "PC2": 17, "PC3": 18, "PA0": 19, "PA1": 20, "EP": 21}
# Fixed pins: PA0 = UPDI; PB2 = USART TX (default) and PA1 = USART TX (alternate) carry the
# bottom and right edges (hardware one-wire USART). Every other signal -- keys K1..K12 (row-
# major order on the board, row 0 = top row), the top and left edge lines (software serial,
# any pin has a pin-change interrupt) and the LED data (bit-banged) -- can use any of the 15
# remaining GPIOs. The board build picks that assignment from the geometry, so that the
# traces leave the 0.4 mm-pitch package without crossing, and stores it in PINMAP_FILE;
# the schematic is drawn from it and the firmware reads it.
FIXED = {"UPDI": "PA0", "DATA_B_MCU": "PB2", "DATA_R_MCU": "PA1"}
FLEX_PORTS = ["PA2", "PA3", "PA4", "PA5", "PA6", "PA7", "PB0", "PB1", "PB3", "PB4", "PB5",
              "PC0", "PC1", "PC2", "PC3"]
FLEX_NETS = [f"K{n + 1}" for n in range(12)] + ["DATA_T_MCU", "DATA_L_MCU", "LED_DIN"]
PINMAP_FILE = os.path.join(os.path.dirname(os.path.abspath(__file__)), "..", "..", "revc-mcu-tile",
                           "pinmap.json")
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
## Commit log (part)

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2026-01-04 Reorganize repository structure and add license layout
2026-01-04 Adding module-tile kicad project
2026-01-04 Added horizontal control line UTF-8 like. Updated capacitor and resistor values.
2026-01-07 starting new topology
2026-01-08 Init VHDL simulation
2026-01-08 Improve logic
2026-01-08 Now VHDL simulation is working. VHDL descirption must be converted to kicad schematic.
2026-01-08 Add real world electronics compatibility for VHDL simulation.
2026-01-10 Add a second simulation
2026-01-10 Start kicad design
2026-02-23 Improving schematics
2026-02-24 Schematics update
2026-02-24 Schematic complete
2026-02-24 Pcb started
2026-02-25 First commit new branch
2026-02-25 Updated cpb with FreeRouting
2026-02-25 Design completed
2026-02-26 Upgrade
2026-02-26 Create gerber files
2026-02-27 Adjust interboard pitch
2026-02-27 Adjust borders
2026-05-26 Start firmware testing
2026-06-14 aggiunti test parziali
2026-06-14 test per integrare logica base con i2c
2026-06-15 aggiornato firmware principale
2026-06-15 Un po' di roba
2026-06-16 Gestione griglia
2026-06-18 Changed directory names
2026-06-19 Added RP firmware dir. Added cmake 3.22 portable.
2026-06-19 Revert "Added RP firmware dir. Added cmake 3.22 portable."
    This reverts commit 45a5596289cfc3bfd2ce563e5ebdb4a24ef075e1.
2026-06-19 better firmware folder structure
2026-06-24 Removed i2c sending. Added keyboard state latching.
2026-06-25 logica di detection dei cambiamenti
2026-06-25 tutto pronto fino alla fsm che manda i dati in midi da una porta fisica
2026-06-29 midi output implemented
2026-06-29 midi uart ok
2026-06-30 midi din working
2026-06-30 fixed polarity and ref pitch
